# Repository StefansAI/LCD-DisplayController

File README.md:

<h1 style="text-align: center;">LCD-DisplayController</h1>
<h2 style="text-align: center;">Controller board to display 2 and 4 lines on LCD modules</h2>
<br>
<div style="text-align: center;">
  
</div>
<br>
The <a href="https://github.com/StefansAI/TTL-6510-Computer">TTL 6510 computer.</a> was designed with connectors for plugging in <a href="https://github.com/StefansAI/HexDisplayController">HexDisplayControllers</a> for displaying register contents etc. Originally these hex displays were used for the micro code steps, instruction register and micro code outputs. Instead of looking up the meaning of instruction codes or the micro code bit group meanings, I decided to switch to multi line displays I had laying around.<br>
The instruction code and micro step counter can be displayed on a 2 line LCD text display module, while the 4 micro step signal groups can better be displayed on a 4 line LCD text display module. 
<br>
<br>
<div style="text-align: center;">
  
</div>
<br>
Both modules can be interfaced in the same way, so the schematics for both can be the same. There are two 8-bit ports to read in from. Since the Arduino processor doesn't have enough pins for both, they are multiplexed to one 8-bit bus.<br>
The LCD module is connected via 4 bit databus as in the example codes for the the Arduino. Then it only needs the resistor for the back light and a potentiometer for the contrast.<br>
<br>
<br>
<div style="text-align: center;">
  
</div>
<br>
The boards in the picture above are hand wired, but to make it nicer and repeatable there needs to be a PCB layout for both cases. The two LCD modules 16x2 and 20x4 have different dimensions and so I changed the design for 2 connectors in parallel, one to be used for the 16x2 module and the other to be used by the 20x4 module.<br>
Another 4-bit header was added to include reading in more bits that are currently wired to single LEDs on the side of the <a href="https://github.com/StefansAI/TTL-6510-Computer">TTL 6510 computer</a> board Rev A. Rev B is now routed to those headers.
<br>
<br>
<div style="text-align: center;">
  
</div>
<br>
The layout is made to plug in the two different sizes of LCD modules and to break off the part only needed for the larger module. The PCB had been made at <a href="www.PCBway.com">PCBway.</a> It was easy to upload the gerbers, get a quote and order the samples. The shipment took just few days.
<br>
<br>
<div style="text-align: center;">
  
</div>
<br>
The blank board as it came from <a href="www.PCBway.com">PCBway.</a> The quality was good and it worked right away as usual.
<br>
<br>
<div style="text-align: center;">
  
</div>
<br>
Board broken off and assembled for LCD 16x2.
<br>
<br>
<div style="text-align: center;">
  
</div>
<br>
Board fully assembled with LCD 16x2.
<br>
<br>
<div style="text-align: center;">
  
</div>
<br>
Board assembled for LCD 20x4.
<br>
<br>
<div style="text-align: center;">
  
</div>
<br>
Board fully assembled with LCD 20x4.
<br>
<br>
<div style="text-align: center;">
  
</div>
<br>
Similar to the <a href="https://github.com/StefansAI/HexDisplayController">HexDisplayController</a>, the processor code is written in the Arduino IDE, then programmed onto the UNO R3 board. The processor is then removed from the UNO board and plugged into the LCD board. Here is a screenshot of the MicroCode_In version containing the 6502 instruction strings.
<br>
<br>
<div style="text-align: center;">
  
</div>
<br>
The second screenshot shows string definitions for the micro code output signals.<br>

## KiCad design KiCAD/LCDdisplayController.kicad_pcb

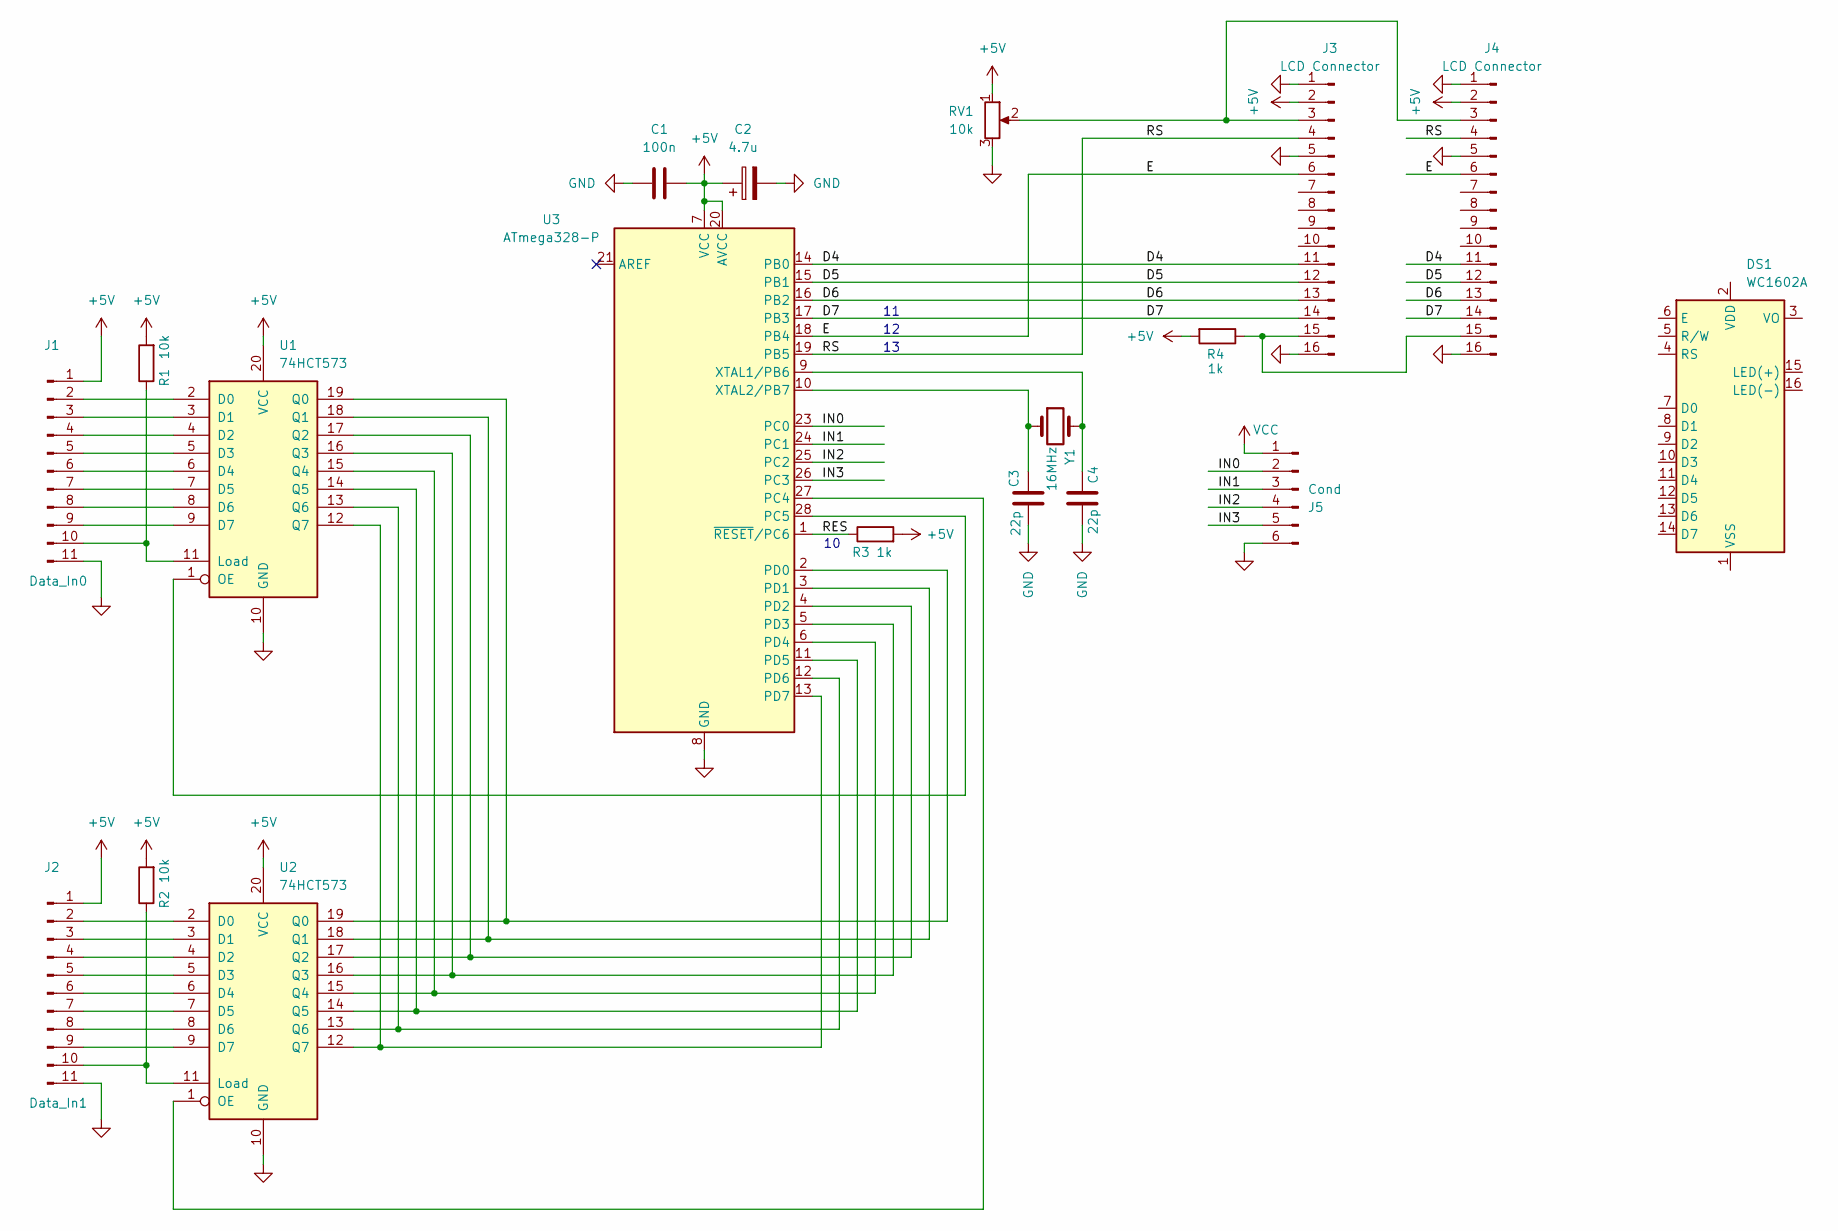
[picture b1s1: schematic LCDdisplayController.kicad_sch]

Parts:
C1: 100n; C_Disc_D4.3mm_W1.9mm_P5.00mm
C2: 4.7u; C_Disc_D4.3mm_W1.9mm_P5.00mm
C3, C4: 22p; C_Disc_D3.0mm_W1.6mm_P2.50mm
DS1: WC1602A
J1: Data_In0; PinHeader_1x11_P2.54mm_Vertical
J2: Data_In1; PinHeader_1x11_P2.54mm_Vertical
J3, J4: LCD Connector; PinHeader_1x16_P2.54mm_Vertical
J5: Cond; PinHeader_1x06_P2.54mm_Vertical
R1, R2: 10k; R_Axial_DIN0204_L3.6mm_D1.6mm_P7.62mm_Horizontal
R3, R4: 1k; R_Axial_DIN0204_L3.6mm_D1.6mm_P7.62mm_Horizontal
RV1: 10k; Potentiometer_Runtron_RM-063_Horizontal
U1, U2: 74HCT573; DIP-20_W7.62mm_Socket
U3: ATmega328-P; DIP-28_W7.62mm_Socket
Y1: 16MHz; Crystal_HC49-U_Vertical

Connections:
/D4: J3.11, J4.11, U3.14 (PB0)
/D5: J3.12, J4.12, U3.15 (PB1)
/D6: J3.13, J4.13, U3.16 (PB2)
/D7: J3.14, J4.14, U3.17 (PB3)
/E: J3.6, J4.6, U3.18 (PB4)
/IN0: J5.2, U3.23 (PC0)
/IN1: J5.3, U3.24 (PC1)
/IN2: J5.4, U3.25 (PC2)
/IN3: J5.5, U3.26 (PC3)
/RES: R3.1, U3.1 (~RESET/PC6)
/RS: J3.4, J4.4, U3.19 (PB5)
GND: C1.1, C2.2, C3.2, C4.2, J1.11, J2.11, J3.1, J3.5, J3.16, J4.1, J4.5, J4.16, J5.6, RV1.3, U1.10 (GND), U2.10 (GND), U3.8 (GND), U3.22 (GND)
unnamed: J1.2, U1.2 (D0)
unnamed: J1.3, U1.3 (D1)
unnamed: J1.4, U1.4 (D2)
unnamed: J1.5, U1.5 (D3)
unnamed: J1.6, U1.6 (D4)
unnamed: J1.7, U1.7 (D5)
unnamed: J1.8, U1.8 (D6)
unnamed: J1.9, U1.9 (D7)
unnamed: J1.10, R1.1, U1.11 (Load)
unnamed: J2.2, U2.2 (D0)
unnamed: J2.3, U2.3 (D1)
unnamed: J2.4, U2.4 (D2)
unnamed: J2.5, U2.5 (D3)
unnamed: J2.6, U2.6 (D4)
unnamed: J2.7, U2.7 (D5)
unnamed: J2.8, U2.8 (D6)
unnamed: J2.9, U2.9 (D7)
unnamed: J2.10, R2.1, U2.11 (Load)
unnamed: J3.3, J4.3, RV1.2
unnamed: J3.15, J4.15, R4.1
unnamed: U1.1 (OE), U3.28 (PC5)
unnamed: U1.19 (Q0), U2.19 (Q0), U3.2 (PD0)
unnamed: U1.18 (Q1), U2.18 (Q1), U3.3 (PD1)
unnamed: U1.17 (Q2), U2.17 (Q2), U3.4 (PD2)
unnamed: U1.16 (Q3), U2.16 (Q3), U3.5 (PD3)
unnamed: U1.15 (Q4), U2.15 (Q4), U3.6 (PD4)
unnamed: U1.14 (Q5), U2.14 (Q5), U3.11 (PD5)
unnamed: U1.13 (Q6), U2.13 (Q6), U3.12 (PD6)
unnamed: U1.12 (Q7), U2.12 (Q7), U3.13 (PD7)
unnamed: U2.1 (OE), U3.27 (PC4)
unnamed: C4.1, U3.9 (XTAL1/PB6), Y1.2
unnamed: C3.1, U3.10 (XTAL2/PB7), Y1.1

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
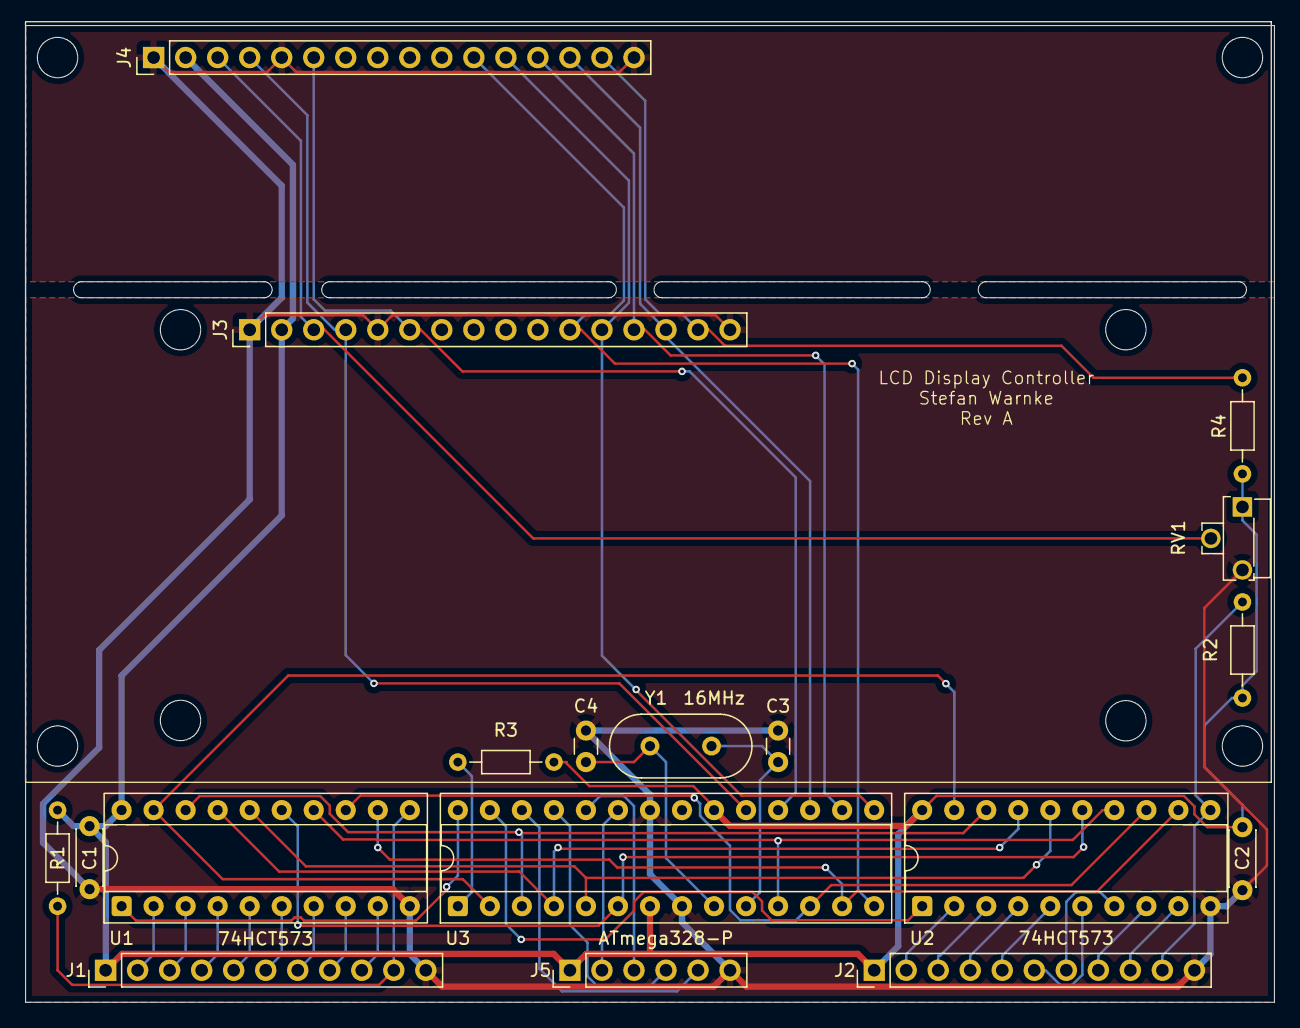
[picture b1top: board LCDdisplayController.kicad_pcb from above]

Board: 2 copper layers, 99.1 x 77.5 mm, 18 parts (0 on the bottom side), 45 nets.

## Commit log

2025-09-10 Initial Check-In
2025-10-03 Updated README and design files
2025-10-05 Replaced main photo
2025-11-15 Updates of KiCad files and README
2025-11-15 Updated layout image
2025-11-15 Correction
2025-12-13 Updating Fab files
2025-12-14 new pics
2025-12-17 Updated pics and codes
2025-12-19 Some corrections
